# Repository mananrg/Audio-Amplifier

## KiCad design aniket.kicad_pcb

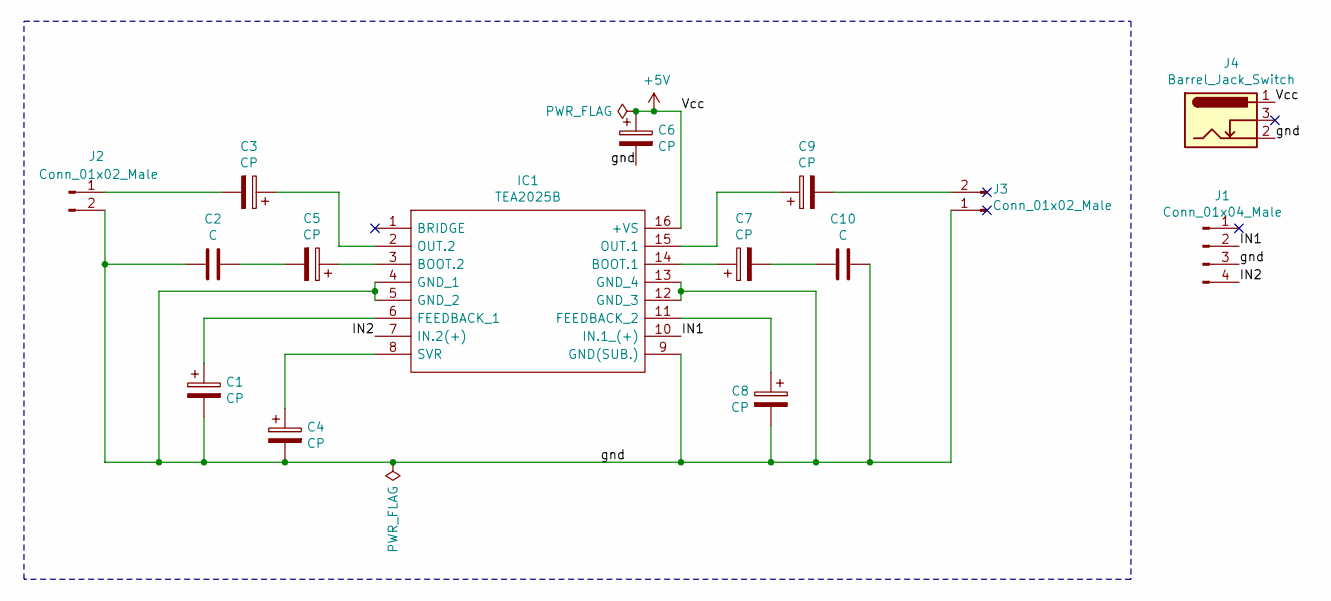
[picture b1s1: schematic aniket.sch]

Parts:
C1, C3, C4, C5, C6, C7, C8, C9: CP; CP_Radial_D10.0mm_P2.50mm
C2, C10: C; CP_Radial_D10.0mm_P2.50mm
IC1: TEA2025B; DIP850W50P254L2000H510Q16N; Manufacturer_Part_Number TEA2025B; Mouser Part Number 511-TEA2025B
J1: Conn_01x04_Male; PinSocket_1x04_P2.54mm_Vertical
J2, J3: Conn_01x02_Male; PinSocket_1x02_P2.54mm_Vertical
J4: Barrel_Jack_Switch; BarrelJack_CUI_PJ-102AH_Horizontal

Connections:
+5V: C6.1, IC1.16 (+VS), J4.1
/IN1: IC1.10 (IN.1_(+)), J1.2
/IN2: IC1.7 (IN.2(+)), J1.4
/gnd: C1.2, C2.1, C4.2, C6.2, C8.2, C10.1, IC1.4 (GND_1), IC1.5 (GND_2), IC1.9 (GND(SUB.)), IC1.12 (GND_3), IC1.13 (GND_4), J1.3, J2.2, J3.1, J4.2
unnamed: C1.1, IC1.6 (FEEDBACK_1)
unnamed: C2.2, C5.2
unnamed: C3.1, IC1.2 (OUT.2)
unnamed: C3.2, J2.1
unnamed: C4.1, IC1.8 (SVR)
unnamed: C5.1, IC1.3 (BOOT.2)
unnamed: C7.1, IC1.14 (BOOT.1)
unnamed: C8.1, IC1.11 (FEEDBACK_2)
unnamed: C9.1, IC1.15 (OUT.1)
unnamed: C9.2, J3.2
unnamed: C7.2, C10.2

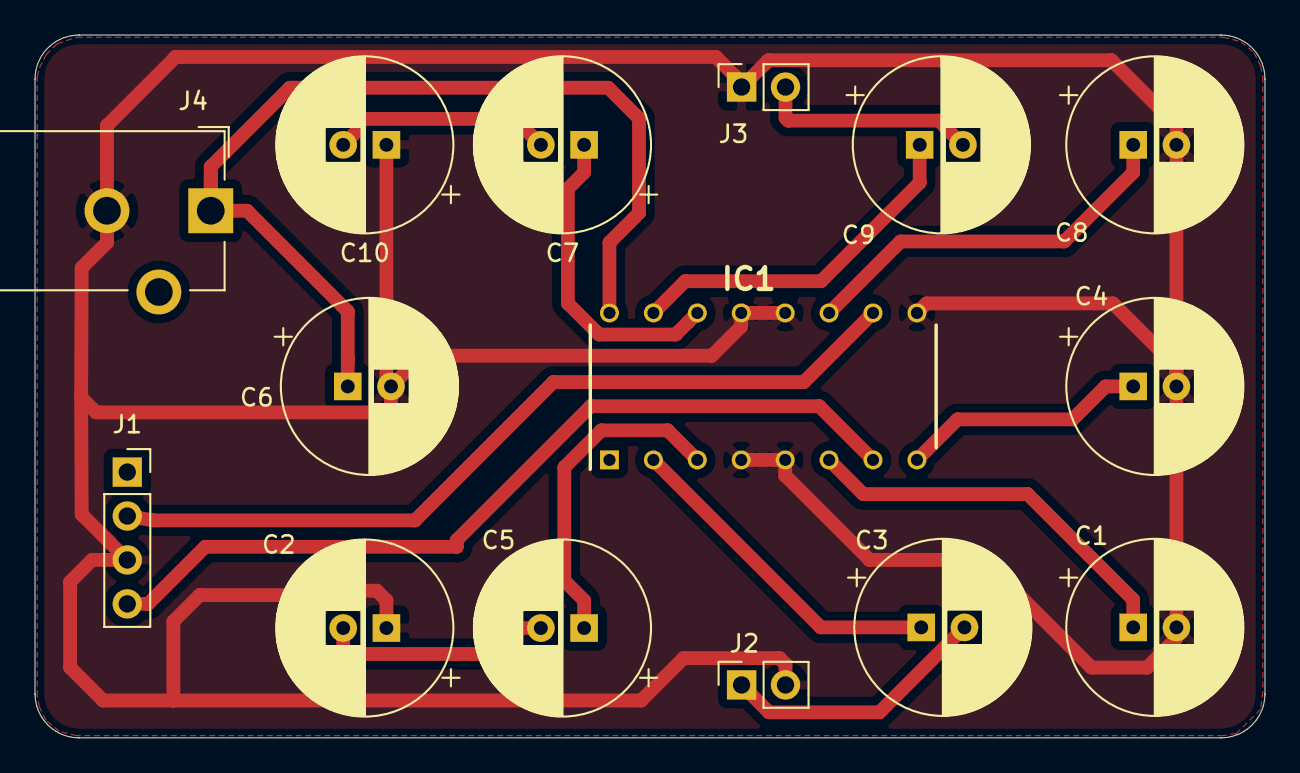
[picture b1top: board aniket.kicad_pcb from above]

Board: 2 copper layers, 71.1 x 40.6 mm, 15 parts (0 on the bottom side), 15 nets.

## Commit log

2019-12-25 1 Two layer 0.8mm
2019-12-25 2 One layer 0.8mm
